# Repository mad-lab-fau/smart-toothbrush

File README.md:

# Smart Toothbrush 

# Overview 
The smart toothbrush is a custom microcontroller board that is built around an **ESP32 processor**. It contains an **Inertial Measurement Unit (IMU)** for tracking linear accelerations with an accelerometer and rotational velocities with a gyroscope. Additionally, a **Real-Time Clock (RTC)** unit is used for timekeeping. The data is written onto a **MircoSD card**. All these components are mounted on a Printed Circuit Board (PCB), providing a compact and efficient design. The electronics are protected from environmental influences by a customised outer case in the shape of a toothbrush. The result is a smart toothbrush with replaceable brushes that can be used for normal tooth brushing.

# Documentation: [Wiki](https://github.com/mad-lab-fau/smart-toothbrush/wiki) 
[Project Overview](https://github.com/mad-lab-fau/smart-toothbrush/wiki/Project-Overview) <br> 
[Hardware-Guide](https://github.com/mad-lab-fau/smart-toothbrush/wiki/Hardware-Guide) <br>
[Software-Guide](https://github.com/mad-lab-fau/smart-toothbrush/wiki/Software-Guide) <br>
[User Manual](https://github.com/mad-lab-fau/smart-toothbrush/wiki/User-Manual)<br>
[Open Issues and Enhancement Opportunities](https://github.com/mad-lab-fau/smart-toothbrush/wiki/Open-Issues-and-Enhancement-Opportunities)<br>

# Studies Using the Smart Toothbrush
The following papers used the Smart Toothbrush in their research:
- *further papers to be added - let us know if you used the Smart Toothbrush in your research!*

# Contributing
We welcome contributions to the Smart Toothbrush project! To contribute, please fork this repository and submit a pull request with your changes. If you run into any issues or have any questions, please open an [issue on Github](https://github.com/mad-lab-fau/smart-toothbrush/issues). If you are using the Smart Toothbrush in your research or project, we would love to hear about it and link your work here!

# License
The Smart Toothbrush is licensed under the MIT License. See the LICENSE file for more information.

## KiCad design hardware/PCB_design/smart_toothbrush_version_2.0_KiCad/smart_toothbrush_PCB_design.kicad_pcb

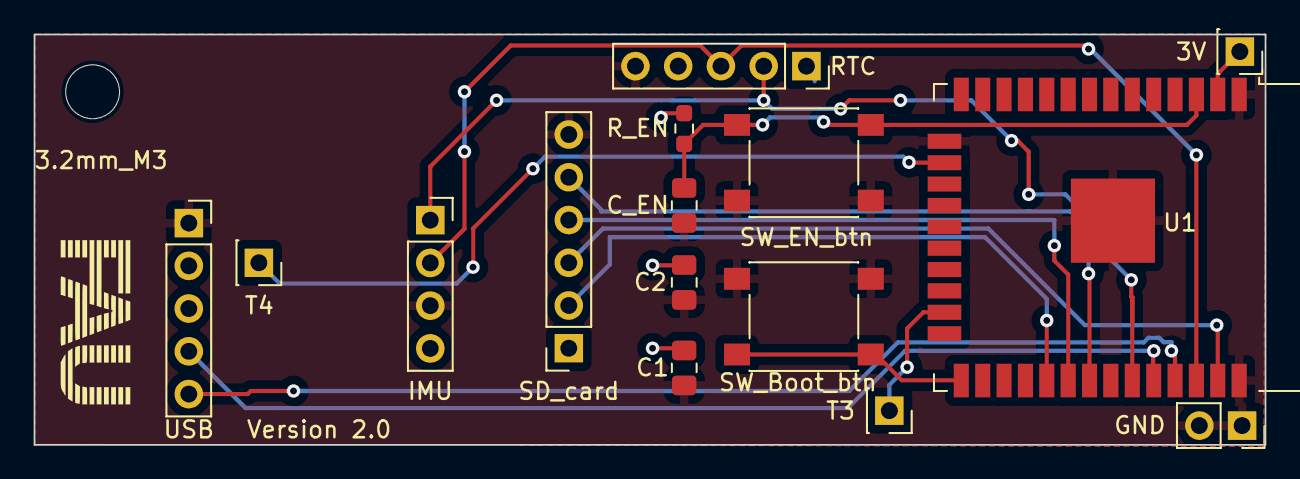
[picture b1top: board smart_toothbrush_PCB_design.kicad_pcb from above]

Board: 2 copper layers, 73.2 x 24.4 mm, 16 parts (0 on the bottom side), 14 nets.

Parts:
3.2mm_M3: MountingHole_3.2mm_M3
3V: Conn_01x01_Male; PinSocket_1x01_P2.54mm_Vertical
C1: 10uF; C_0805_2012Metric_Pad1.18x1.45mm_HandSolder
C2: 0.1uF; C_0805_2012Metric_Pad1.18x1.45mm_HandSolder
C_EN: 0.1uF; C_0805_2012Metric_Pad1.18x1.45mm_HandSolder
GND: Conn_01x02_Pin; PinSocket_1x02_P2.54mm_Vertical
IMU: Conn_01x04_Male; PinSocket_1x04_P2.54mm_Vertical
RTC: Conn_01x05_Male; PinSocket_1x05_P2.54mm_Vertical
R_EN: 10K; R_0603_1608Metric_Pad0.98x0.95mm_HandSolder
SD_card: Conn_01x06_Male; PinSocket_1x06_P2.54mm_Vertical
SW_Boot_btn: SW_Push; SW_Push_1P1T_NO_6x6mm_H9.5mm
SW_EN_btn: SW_Push; SW_Push_1P1T_NO_6x6mm_H9.5mm
T3, T4: Conn_01x01_Male; PinSocket_1x01_P2.54mm_Vertical
U1: ESP32-WROOM-32
USB: Conn_01x05_Male; PinSocket_1x05_P2.54mm_Vertical

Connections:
+3V3: 3V.1, C1.1, C2.1, IMU.4, RTC.1, R_EN.1, SD_card.1, U1.2 (VDD), USB.3
/EN: C_EN.1, R_EN.2, SW_EN_btn.2, U1.3 (EN)
/IO0: SW_Boot_btn.2, U1.25 (IO0)
/IO5: SD_card.2, U1.29 (IO5)
/IO18: SD_card.4, U1.30 (IO18)
/IO19: SD_card.5, U1.31 (IO19)
/IO21: IMU.1, RTC.2, U1.33 (IO21)
/IO22: IMU.2, RTC.3, U1.36 (IO22)
/IO23: SD_card.3, U1.37 (IO23)
/RXD0: U1.34 (RXD0/IO3), USB.4
/T3: T3.1, U1.23 (IO15)
/T4: T4.1, U1.16 (IO13)
/TXD0: U1.35 (TXD0/IO1), USB.5
GND: C1.2, C2.2, C_EN.2, GND.1, GND.2, IMU.3, RTC.5, SD_card.6, SW_Boot_btn.1, SW_EN_btn.1, U1.1 (GND), U1.15 (GND), U1.38 (GND), U1.39 (GND), USB.1

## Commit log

2024-05-01 Added LICENSE
2024-05-01 Create LICENSE
2024-05-01 Added all project files
2024-09-03 Fixed bug: Wrong conversion of the gyroscope values
